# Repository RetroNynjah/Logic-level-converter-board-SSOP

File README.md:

# Logic level converter board (SSOP)
A bi-directional high-speed TTL-Compatible level shifter board 5V ⇄ 3V3 for tinkering

This fork replaces the currently hard to find TSSOP package with the more available SSOP package.  
Only a few small adjustments had to be made to make room for the larger chip.
***

PART  | Value       | Description
---| ---------------| -------
D1 | 2.54 mm pin pitch | LED Diode (optional Power on/off indicator)
R1 | 100-330 Ohm | 1206 (populate if D1, calculate suitable resistor value to use with D1)
C1 | 10-100 uF   | 1210
C2 | 0.1 uF      | 1206
U1 | SN74CBTD16211DL https://www.ti.com/lit/ds/symlink/sn74cbtd16211.pdf| SSOP-56_7.5x18.5mm_P0.635mm
 | Pushbutton switch SW_7x7x12mm_DPDT
 | Barrel Jack 5.5x2.1mm
 | Power +5V center pin positive or via pinheader (verify polarity before connecting)
 | 2.54 mm jumpers to enable/disable /1OE (first 12-bits) and /2OE (second 12-bits), either enable via jumper to GND or disable via VCC.
 | 2.54 mm jumpers to disable unused inputs via jumper to GND.
 | A lot of 2.54mm pinheader strips. 

Happy Tinkerin'

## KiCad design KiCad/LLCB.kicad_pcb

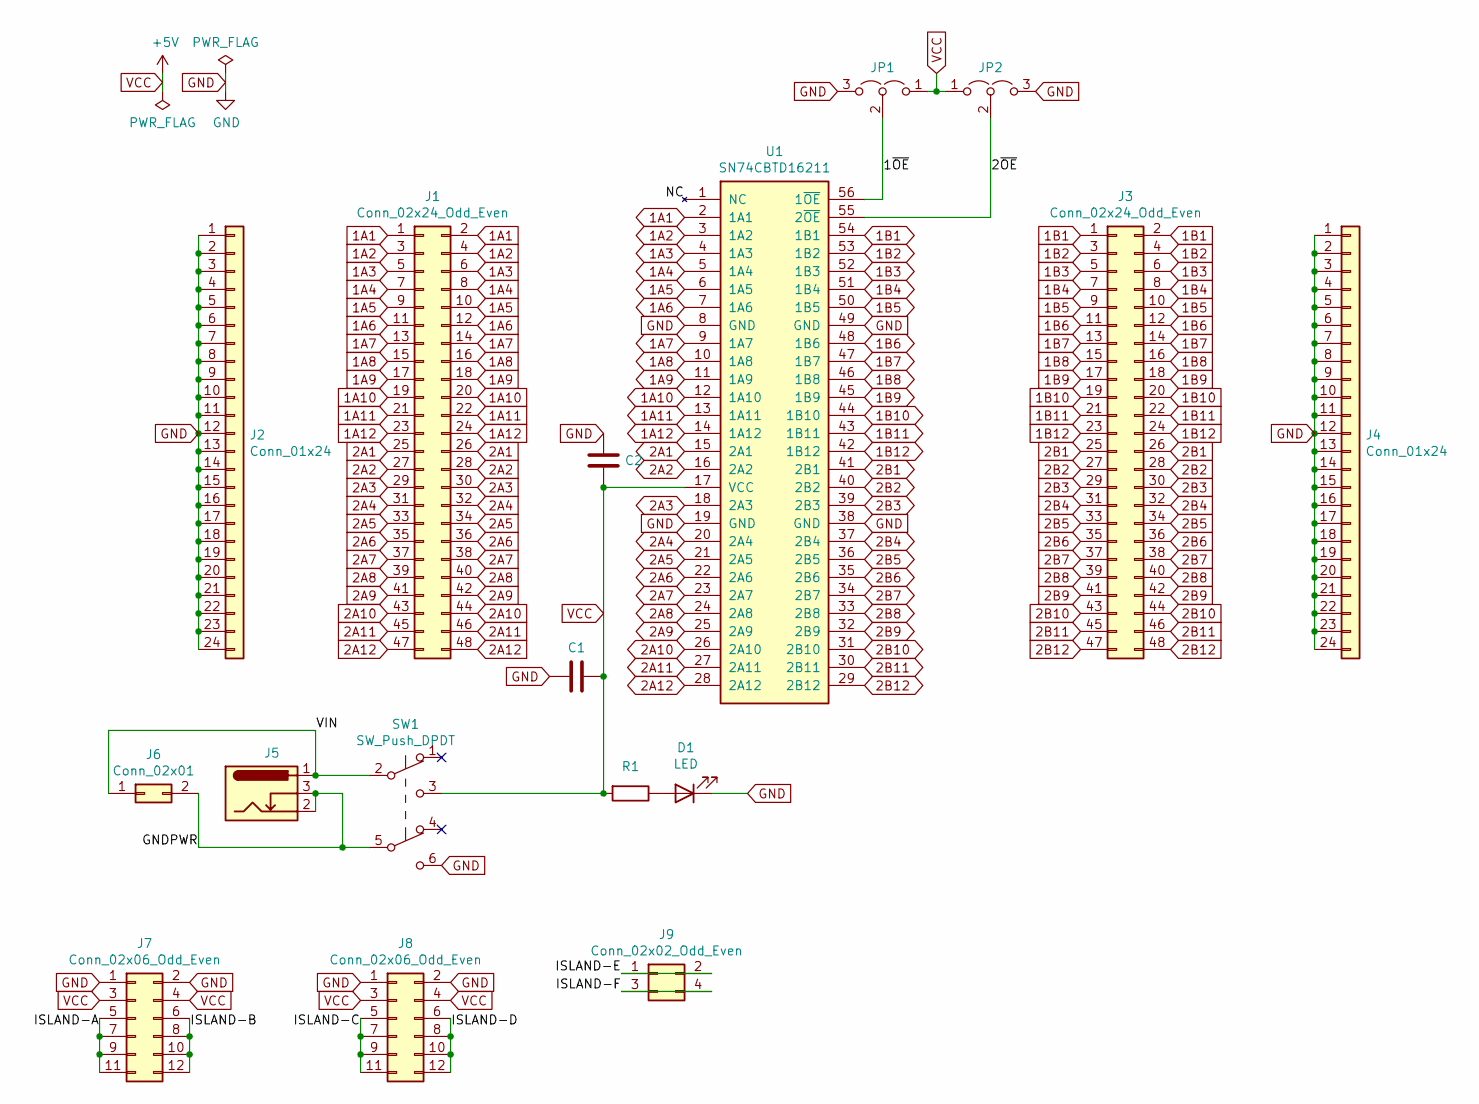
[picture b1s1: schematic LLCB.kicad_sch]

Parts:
C1: C; C_1210_3225Metric_Pad1.42x2.65mm_HandSolder
C2: C; C_1206_3216Metric_Pad1.42x1.75mm_HandSolder
D1: LED; LED_D3.0mm
J1, J3: Conn_02x24_Odd_Even; PinHeader_2x24_P2.54mm_Vertical
J2, J4: Conn_01x24; PinHeader_1x24_P2.54mm_Vertical
J5: Barrel_Jack_Switch; BarrelJack_Horizontal
J6: Conn_02x01; PinHeader_2x01_P2.54mm_Vertical
J7, J8: Conn_02x06_Odd_Even; PinHeader_2x06_P2.54mm_Vertical
J9: Conn_02x02_Odd_Even; PinHeader_2x02_P2.54mm_Vertical
JP1, JP2: Jumper_3_Open; PinHeader_1x03_P2.54mm_Vertical
R1: R; R_1206_3216Metric_Pad1.42x1.75mm_HandSolder
SW1: SW_Push_DPDT; SW_Push_THT_7x7x12mm_DPDT
U1: SN74CBTD16211; SSOP-56_7.5x18.5mm_P0.635mm

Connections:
1A1: J1.1, J1.2, U1.2 (1A1)
1A2: J1.3, J1.4, U1.3 (1A2)
1A3: J1.5, J1.6, U1.4 (1A3)
1A4: J1.7, J1.8, U1.5 (1A4)
1A5: J1.9, J1.10, U1.6 (1A5)
1A6: J1.11, J1.12, U1.7 (1A6)
1A7: J1.13, J1.14, U1.9 (1A7)
1A8: J1.15, J1.16, U1.10 (1A8)
1A9: J1.17, J1.18, U1.11 (1A9)
1A10: J1.19, J1.20, U1.12 (1A10)
1A11: J1.21, J1.22, U1.13 (1A11)
1A12: J1.23, J1.24, U1.14 (1A12)
1B1: J3.1, J3.2, U1.54 (1B1)
1B2: J3.3, J3.4, U1.53 (1B2)
1B3: J3.5, J3.6, U1.52 (1B3)
1B4: J3.7, J3.8, U1.51 (1B4)
1B5: J3.9, J3.10, U1.50 (1B5)
1B6: J3.11, J3.12, U1.48 (1B6)
1B7: J3.13, J3.14, U1.47 (1B7)
1B8: J3.15, J3.16, U1.46 (1B8)
1B9: J3.17, J3.18, U1.45 (1B9)
1B10: J3.19, J3.20, U1.44 (1B10)
1B11: J3.21, J3.22, U1.43 (1B11)
1B12: J3.23, J3.24, U1.42 (1B12)
2A1: J1.25, J1.26, U1.15 (2A1)
2A2: J1.27, J1.28, U1.16 (2A2)
2A3: J1.29, J1.30, U1.18 (2A3)
2A4: J1.31, J1.32, U1.20 (2A4)
2A5: J1.33, J1.34, U1.21 (2A5)
2A6: J1.35, J1.36, U1.22 (2A6)
2A7: J1.37, J1.38, U1.23 (2A7)
2A8: J1.39, J1.40, U1.24 (2A8)
2A9: J1.41, J1.42, U1.25 (2A9)
2A10: J1.43, J1.44, U1.26 (2A10)
2A11: J1.45, J1.46, U1.27 (2A11)
2A12: J1.47, J1.48, U1.28 (2A12)
2B1: J3.25, J3.26, U1.41 (2B1)
2B2: J3.27, J3.28, U1.40 (2B2)
2B3: J3.29, J3.30, U1.39 (2B3)
2B4: J3.31, J3.32, U1.37 (2B4)
2B5: J3.33, J3.34, U1.36 (2B5)
2B6: J3.35, J3.36, U1.35 (2B6)
2B7: J3.37, J3.38, U1.34 (2B7)
2B8: J3.39, J3.40, U1.33 (2B8)
2B9: J3.41, J3.42, U1.32 (2B9)
2B10: J3.43, J3.44, U1.31 (2B10)
2B11: J3.45, J3.46, U1.30 (2B11)
2B12: J3.47, J3.48, U1.29 (2B12)
/1~OE: JP1.2 (C), U1.56 (1~OE)
/2~OE: JP2.2 (C), U1.55 (2~OE)
/GNDPWR: J5.2, J5.3, J6.2, SW1.5 (B)
/ISLAND-A: J7.5, J7.7, J7.9, J7.11
/ISLAND-B: J7.6, J7.8, J7.10, J7.12
/ISLAND-C: J8.5, J8.7, J8.9, J8.11
/ISLAND-D: J8.6, J8.8, J8.10, J8.12
/ISLAND-E: J9.1, J9.2
/ISLAND-F: J9.3, J9.4
/VIN: J5.1, J6.1, SW1.2 (B)
GND: C1.2, C2.1, D1.1 (K), J2.1, J2.2, J2.3, J2.4, J2.5, J2.6, J2.7, J2.8, J2.9, J2.10, J2.11, J2.12, J2.13, J2.14, J2.15, J2.16, J2.17, J2.18, J2.19, J2.20, J2.21, J2.22, J2.23, J2.24, J4.1, J4.2, J4.3, J4.4, J4.5, J4.6, J4.7, J4.8, J4.9, J4.10, J4.11, J4.12, J4.13, J4.14, J4.15, J4.16, J4.17, J4.18, J4.19, J4.20, J4.21, J4.22, J4.23, J4.24, J7.1, J7.2, J8.1, J8.2, JP1.3 (B), JP2.3 (B), SW1.6 (C), U1.8 (GND), U1.19 (GND), U1.38 (GND), U1.49 (GND)
unnamed: D1.2 (A), R1.1
VCC: C1.1, C2.2, J7.3, J7.4, J8.3, J8.4, JP1.1 (A), JP2.1 (A), R1.2, SW1.3 (C), U1.17 (VCC)

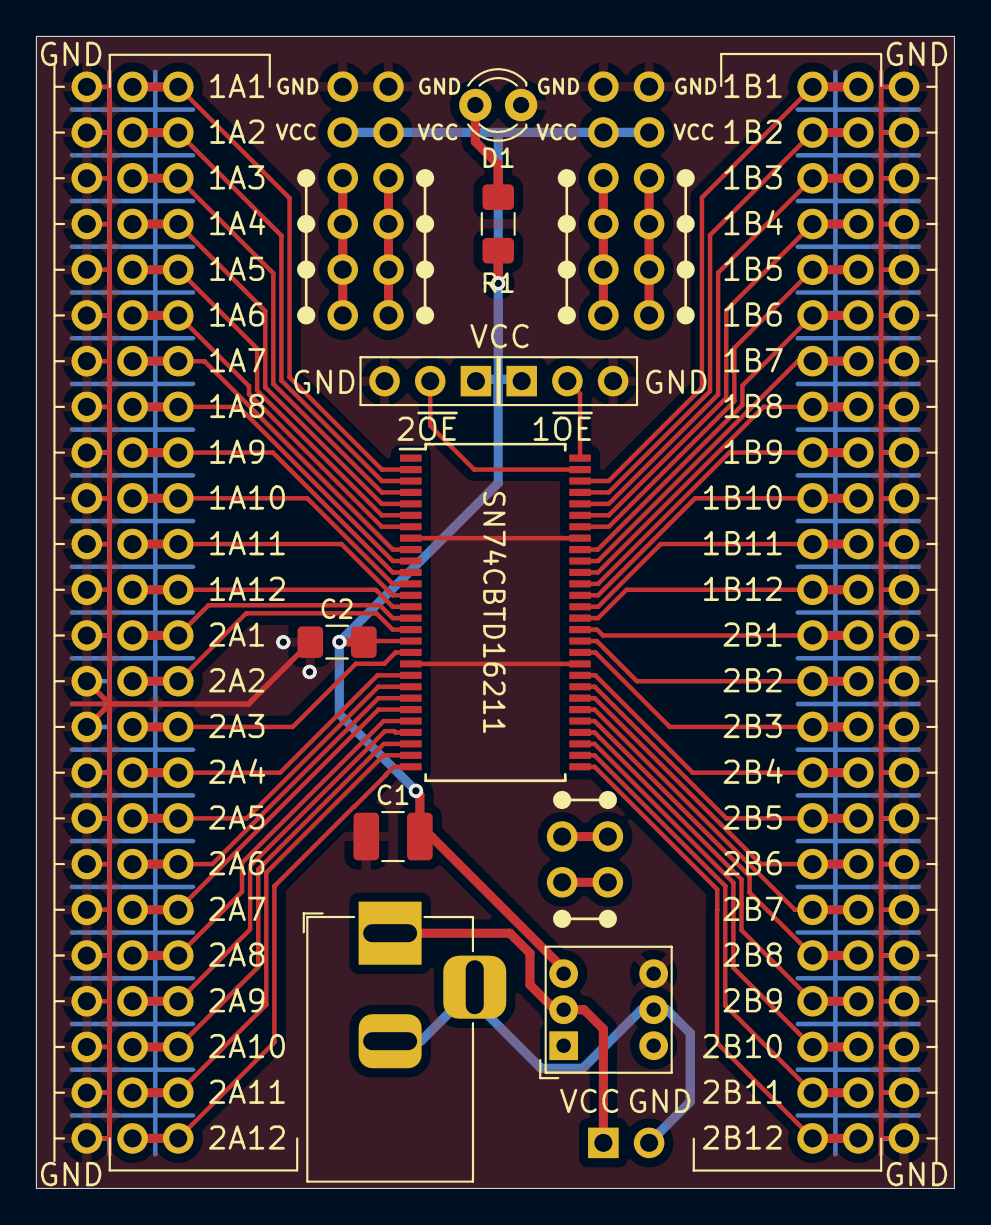
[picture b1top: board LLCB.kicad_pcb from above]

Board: 2 copper layers, 51.0 x 64.0 mm, 17 parts (0 on the bottom side), 61 nets.

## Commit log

2023-07-18 Created SSOP variant of board
2023-07-18 Updated images and readme
